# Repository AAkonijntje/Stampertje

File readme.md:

Project AAkonijntjes

## Abstract
In dit project maken we een robot genaamd Stampertje.
Axel Willekens en Arno Plaetinck aka AAkonijntjes

## Documentation

## Authors

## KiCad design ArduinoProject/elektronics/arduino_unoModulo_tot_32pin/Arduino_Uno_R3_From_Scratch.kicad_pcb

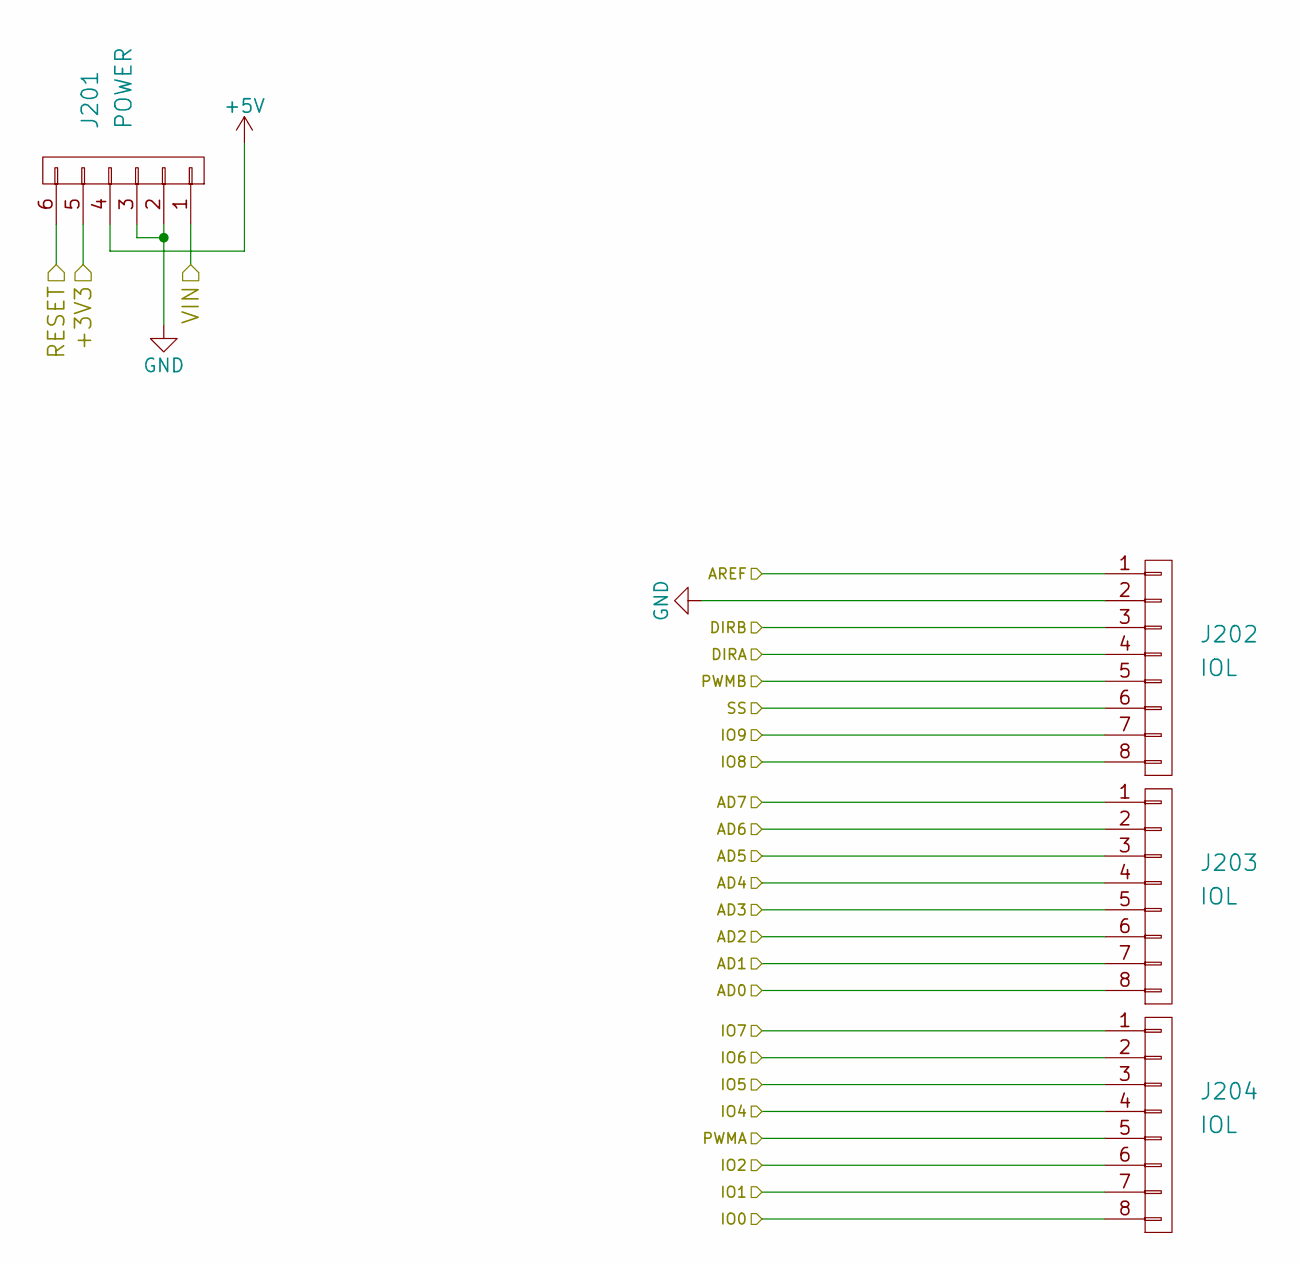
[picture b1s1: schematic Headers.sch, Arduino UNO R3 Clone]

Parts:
J201: POWER; Socket_Strip_Straight_1x06_Pitch2.54mm
J202, J203, J204: IOL; Socket_Strip_Straight_1x08_Pitch2.54mm

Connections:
328P_ICSP_MISO: J202.4; also elsewhere on the board
328P_ICSP_MOSI: J202.5; also elsewhere on the board
328P_ICSP_SCK: J202.3; also elsewhere on the board
+5V: J201.4; also elsewhere on the board
/ATMEGA328P/AD0: J203.8; also elsewhere on the board
/ATMEGA328P/AD1: J203.7; also elsewhere on the board
/ATMEGA328P/AD2: J203.6; also elsewhere on the board
/ATMEGA328P/AD3: J203.5; also elsewhere on the board
/ATMEGA328P/AD4: J203.4; also elsewhere on the board
/ATMEGA328P/AD5: J203.3; also elsewhere on the board
/ATMEGA328P/AD6: J203.2; also elsewhere on the board
/ATMEGA328P/AD7: J203.1; also elsewhere on the board
/ATMEGA328P/AREF: J202.1; also elsewhere on the board
/ATMEGA328P/IO0: J204.8; also elsewhere on the board
/ATMEGA328P/IO1: J204.7; also elsewhere on the board
/ATMEGA328P/IO2: J204.6; also elsewhere on the board
/ATMEGA328P/IO4: J204.4; also elsewhere on the board
/ATMEGA328P/IO5: J204.3; also elsewhere on the board
/ATMEGA328P/IO6: J204.2; also elsewhere on the board
/ATMEGA328P/IO7: J204.1; also elsewhere on the board
/ATMEGA328P/IO8: J202.8; also elsewhere on the board
/ATMEGA328P/IO9: J202.7; also elsewhere on the board
/ATMEGA328P/PWMA: J204.5; also elsewhere on the board
/ATMEGA328P/RESET: J201.6; also elsewhere on the board
/ATMEGA328P/SS: J202.6; also elsewhere on the board
/Headers/+3V3: J201.5; also elsewhere on the board
/Headers/VIN: J201.1; also elsewhere on the board
GND: J201.2, J201.3, J202.2; also elsewhere on the board

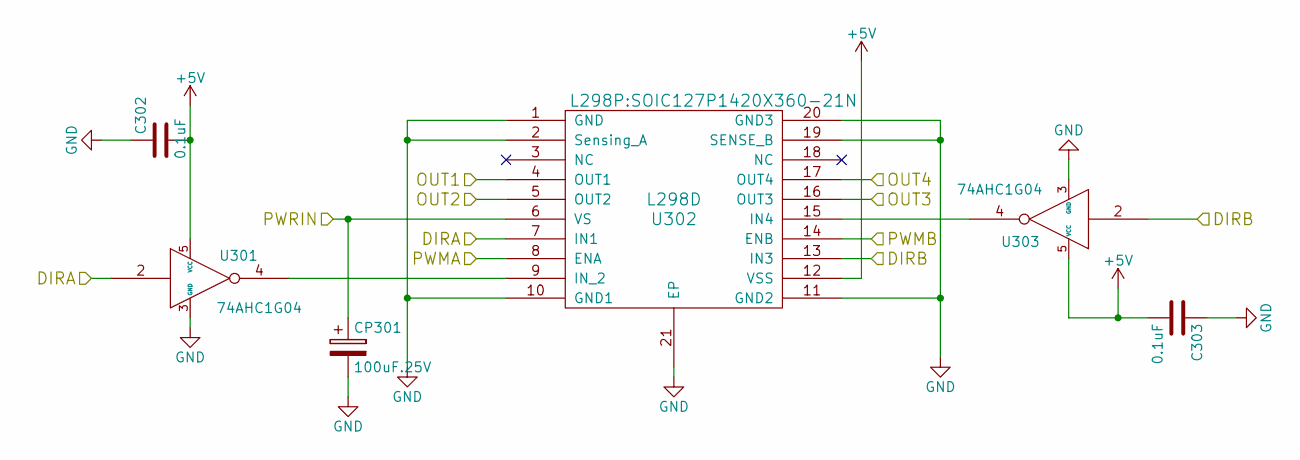
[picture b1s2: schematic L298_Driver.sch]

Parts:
C302, C303: 0.1uF; C_0805
CP301: 100uF.25V; CP_Elec_6.3x5.3
U301, U303: 74AHC1G04; SOT65P210X110-5N
U302: L298D; SOIC127P1420X360-21N

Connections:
328P_ICSP_MISO: U301.2, U302.7 (IN1); also elsewhere on the board
328P_ICSP_MOSI: U302.14 (ENB); also elsewhere on the board
328P_ICSP_SCK: U302.13 (IN3), U303.2; also elsewhere on the board
+5V: C302.2, C303.2, U301.5 (VCC), U302.12 (VSS), U303.5 (VCC); also elsewhere on the board
/ATMEGA328P/PWMA: U302.8 (ENA); also elsewhere on the board
/L298_Driver./OUT1: U302.4 (OUT1); also elsewhere on the board
/L298_Driver./OUT2: U302.5 (OUT2); also elsewhere on the board
/L298_Driver./OUT3: U302.16 (OUT3); also elsewhere on the board
/L298_Driver./OUT4: U302.17 (OUT4); also elsewhere on the board
/L298_Driver./PWRIN: CP301.1, U302.6 (VS); also elsewhere on the board
GND: C302.1, C303.1, CP301.2, U301.3 (GND), U302.1 (GND), U302.2 (Sensing_A), U302.10 (GND1), U302.11 (GND2), U302.19 (SENSE_B), U302.20 (GND3), U302.21 (EP), U303.3 (GND); also elsewhere on the board
unnamed: U301.4, U302.9 (IN_2)
unnamed: U302.15 (IN4), U303.4

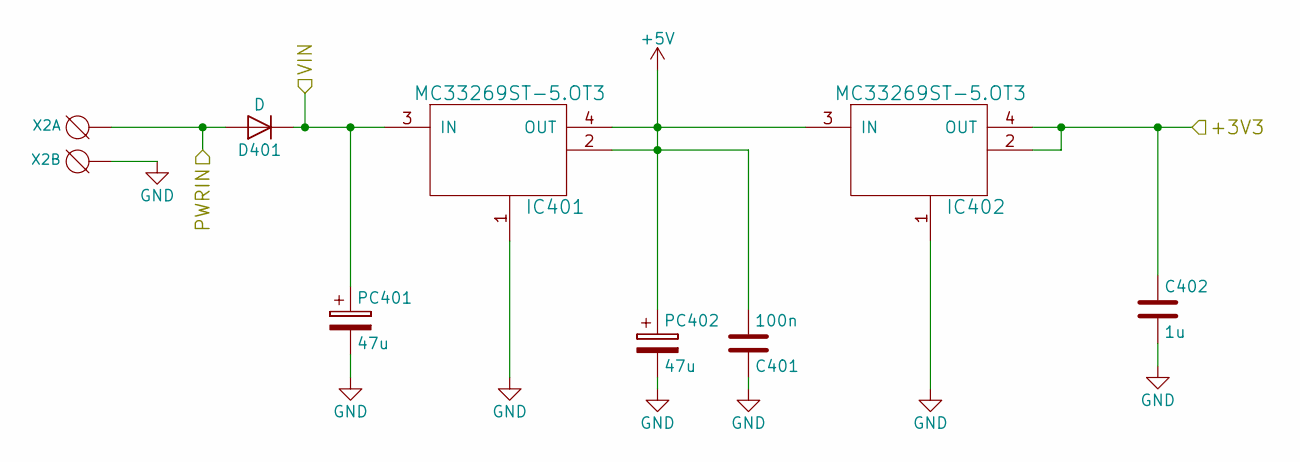
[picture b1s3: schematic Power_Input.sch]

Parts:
C401: 100n; C_0805
C402: 1u; C_0805
D401: D; D_MiniMELF_Handsoldering
IC401, IC402: MC33269ST-5.OT3; SOT230P700X180-4N
PC401, PC402: 47u; CP_Elec_6.3x5.3
X2: DG3XX-02-3.5; degson-DG350-3.5-02P

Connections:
+5V: C401.2, IC401.2, IC401.4 (OUT), IC402.3 (IN), PC402.1; also elsewhere on the board
/Headers/+3V3: C402.1, IC402.2, IC402.4 (OUT); also elsewhere on the board
/Headers/VIN: D401.1 (K), IC401.3 (IN), PC401.1; also elsewhere on the board
/L298_Driver./PWRIN: D401.2 (A), X2.1; also elsewhere on the board
GND: C401.1, C402.2, IC401.1, IC402.1, PC401.2, PC402.2, X2.2; also elsewhere on the board

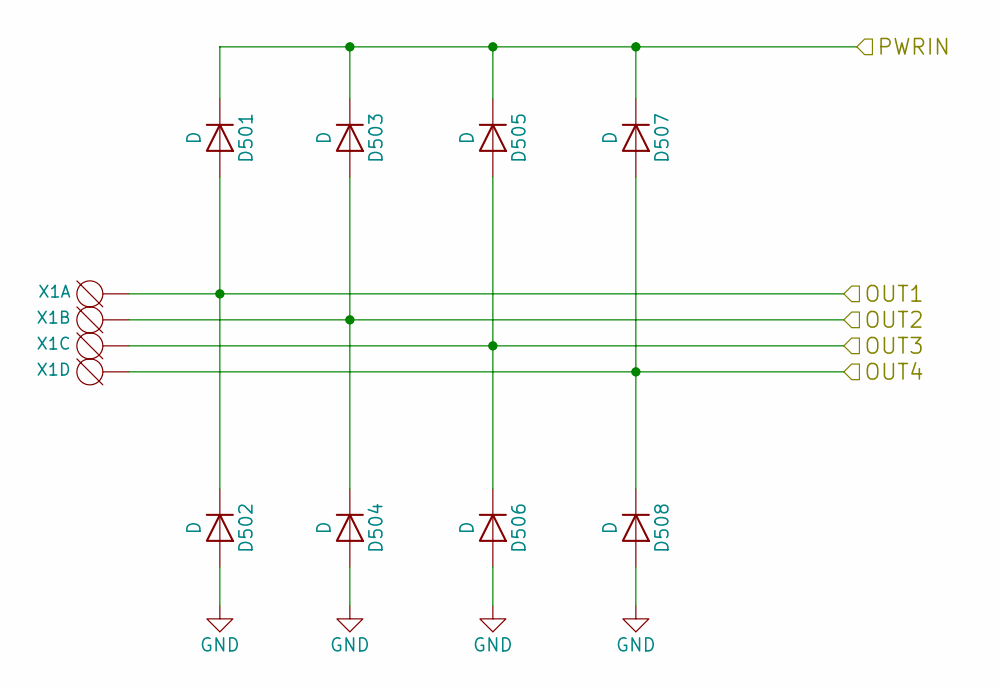
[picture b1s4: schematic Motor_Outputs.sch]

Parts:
D501, D502, D503, D504, D505, D506, D507, D508: D; DIOM5437X240N
X1: DG3XX-04-3.5; degson-DG350-3.5-04P

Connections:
/L298_Driver./OUT1: D501.2 (A), D502.1 (K), X1.1; also elsewhere on the board
/L298_Driver./OUT2: D503.2 (A), D504.1 (K), X1.2; also elsewhere on the board
/L298_Driver./OUT3: D505.2 (A), D506.1 (K), X1.3; also elsewhere on the board
/L298_Driver./OUT4: D507.2 (A), D508.1 (K), X1.4; also elsewhere on the board
/L298_Driver./PWRIN: D501.1 (K), D503.1 (K), D505.1 (K), D507.1 (K); also elsewhere on the board
GND: D502.2 (A), D504.2 (A), D506.2 (A), D508.2 (A); also elsewhere on the board

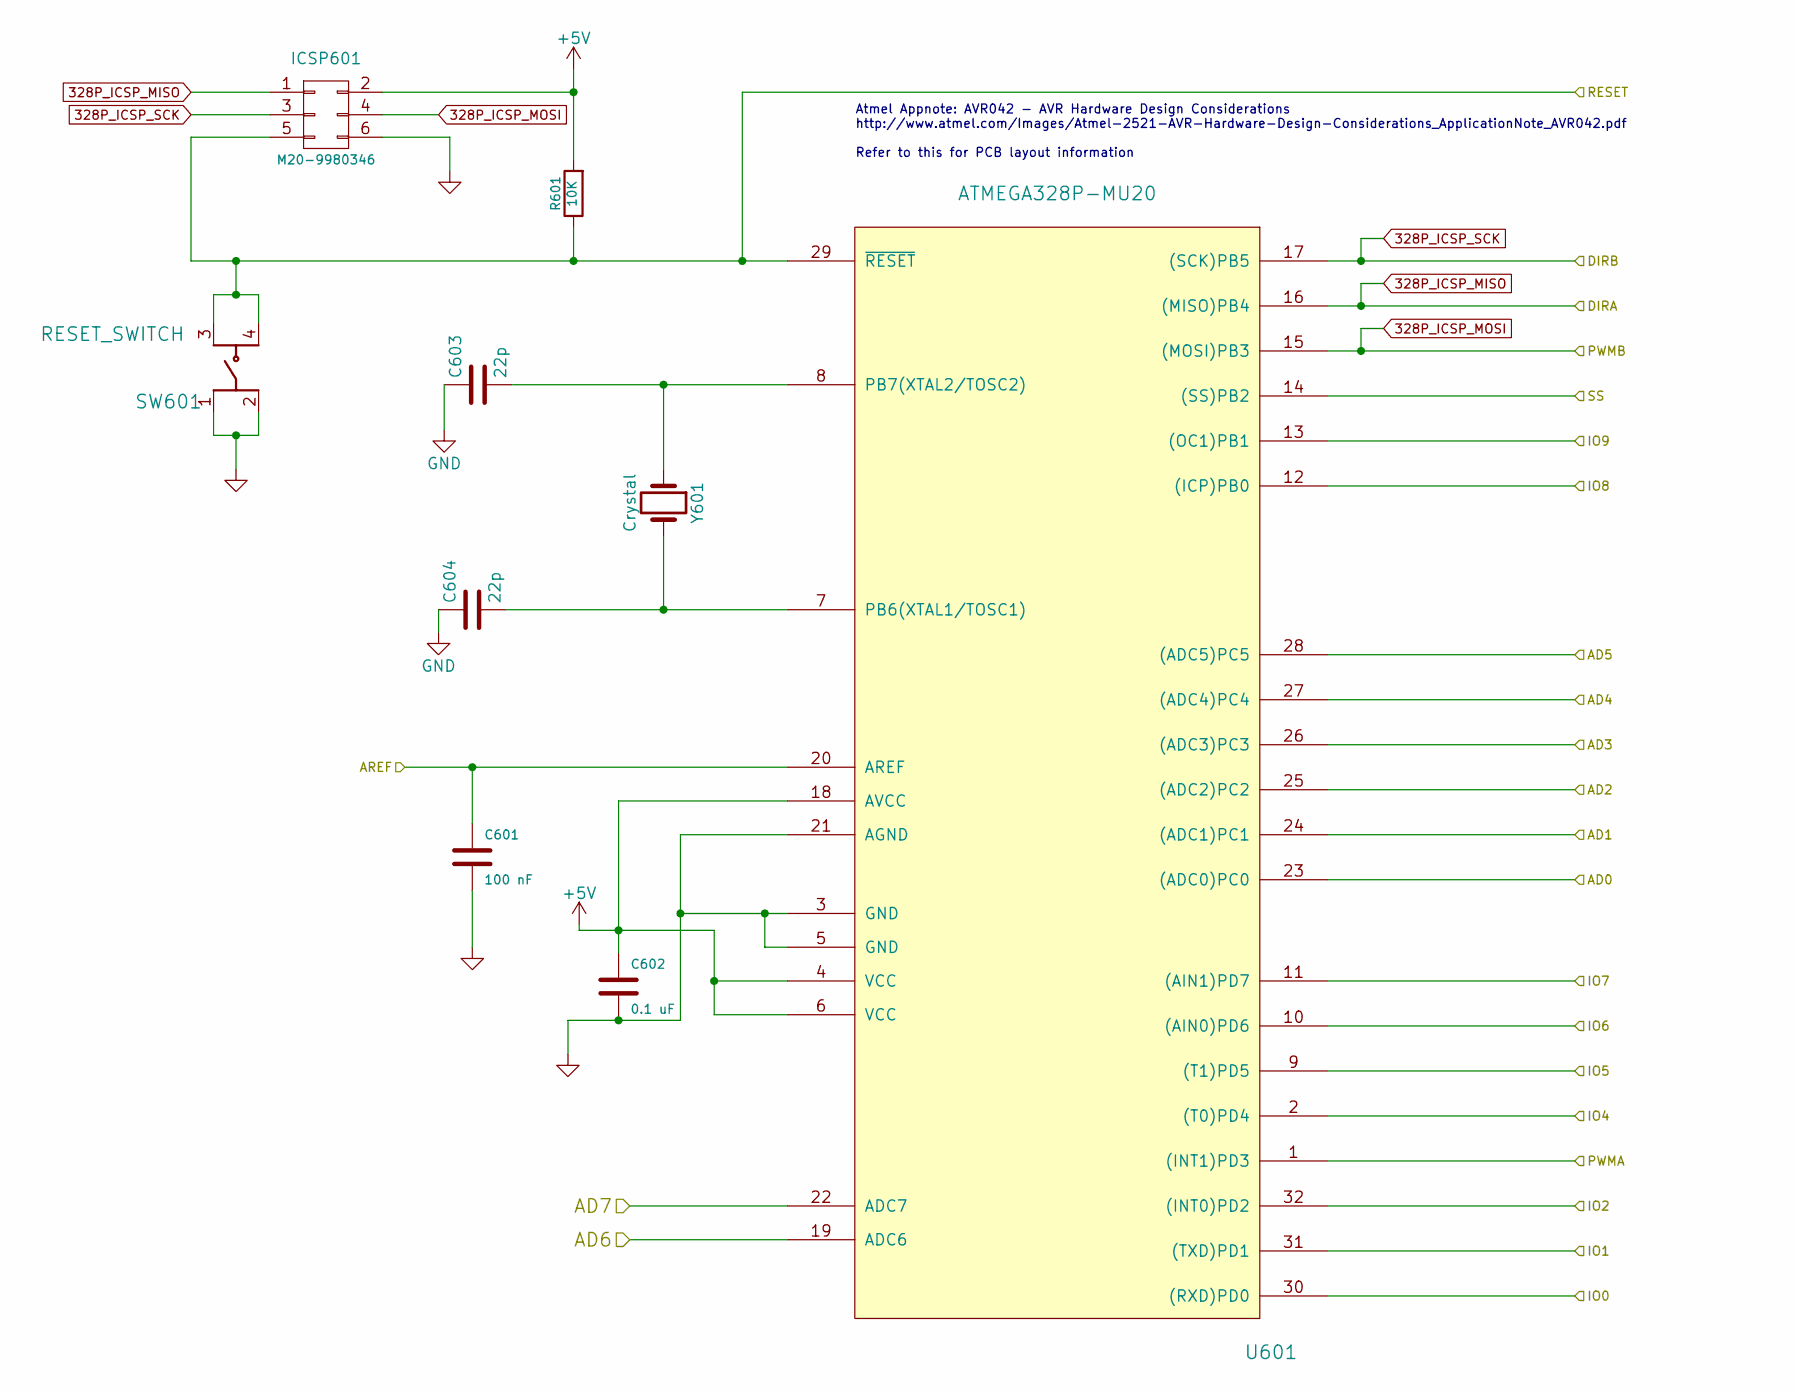
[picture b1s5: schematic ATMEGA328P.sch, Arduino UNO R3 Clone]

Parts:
C601: 100 nF; C_0805
C602: 0.1 uF; C_0805
C603, C604: 22p; C_0805
ICSP601: M20-9980346; HDRV6W64P254_2X3_762X508X868P
R601: 10K; R_0805
SW601: RESET_SWITCH; FSM-SWITCH
U601: ATMEGA328P-MU20; QFP80P900X900X120-32N
Y601: Crystal; HC%2f49US-(AT49)_1

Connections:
328P_ICSP_MISO: ICSP601.1, U601.16 ((MISO)PB4); also elsewhere on the board
328P_ICSP_MOSI: ICSP601.4, U601.15 ((MOSI)PB3); also elsewhere on the board
328P_ICSP_SCK: ICSP601.3, U601.17 ((SCK)PB5); also elsewhere on the board
+5V: C602.1, ICSP601.2, R601.2, U601.4 (VCC), U601.6 (VCC), U601.18 (AVCC); also elsewhere on the board
/ATMEGA328P/AD0: U601.23 ((ADC0)PC0); also elsewhere on the board
/ATMEGA328P/AD1: U601.24 ((ADC1)PC1); also elsewhere on the board
/ATMEGA328P/AD2: U601.25 ((ADC2)PC2); also elsewhere on the board
/ATMEGA328P/AD3: U601.26 ((ADC3)PC3); also elsewhere on the board
/ATMEGA328P/AD4: U601.27 ((ADC4)PC4); also elsewhere on the board
/ATMEGA328P/AD5: U601.28 ((ADC5)PC5); also elsewhere on the board
/ATMEGA328P/AD6: U601.19 (ADC6); also elsewhere on the board
/ATMEGA328P/AD7: U601.22 (ADC7); also elsewhere on the board
/ATMEGA328P/AREF: C601.1, U601.20 (AREF); also elsewhere on the board
/ATMEGA328P/IO0: U601.30 ((RXD)PD0); also elsewhere on the board
/ATMEGA328P/IO1: U601.31 ((TXD)PD1); also elsewhere on the board
/ATMEGA328P/IO2: U601.32 ((INT0)PD2); also elsewhere on the board
/ATMEGA328P/IO4: U601.2 ((T0)PD4); also elsewhere on the board
/ATMEGA328P/IO5: U601.9 ((T1)PD5); also elsewhere on the board
/ATMEGA328P/IO6: U601.10 ((AIN0)PD6); also elsewhere on the board
/ATMEGA328P/IO7: U601.11 ((AIN1)PD7); also elsewhere on the board
/ATMEGA328P/IO8: U601.12 ((ICP)PB0); also elsewhere on the board
/ATMEGA328P/IO9: U601.13 ((OC1)PB1); also elsewhere on the board
/ATMEGA328P/PWMA: U601.1 ((INT1)PD3); also elsewhere on the board
/ATMEGA328P/RESET: ICSP601.5, R601.1, SW601.3, SW601.4, U601.29 (~RESET); also elsewhere on the board
/ATMEGA328P/SS: U601.14 ((SS)PB2); also elsewhere on the board
GND: C601.2, C602.2, C603.1, C604.1, ICSP601.6, SW601.1, SW601.2, U601.3 (GND), U601.5 (GND), U601.21 (AGND); also elsewhere on the board
unnamed: C603.2, U601.8 (PB7(XTAL2/TOSC2)), Y601.1
unnamed: C604.2, U601.7 (PB6(XTAL1/TOSC1)), Y601.2

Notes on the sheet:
Atmel Appnote: AVR042 - AVR Hardware Design Considerations http://www.atmel.com/Images/Atmel-2521-AVR-Hardware-Design-Considerations_ApplicationNote_AVR042.pdf Refer to this for PCB layout information

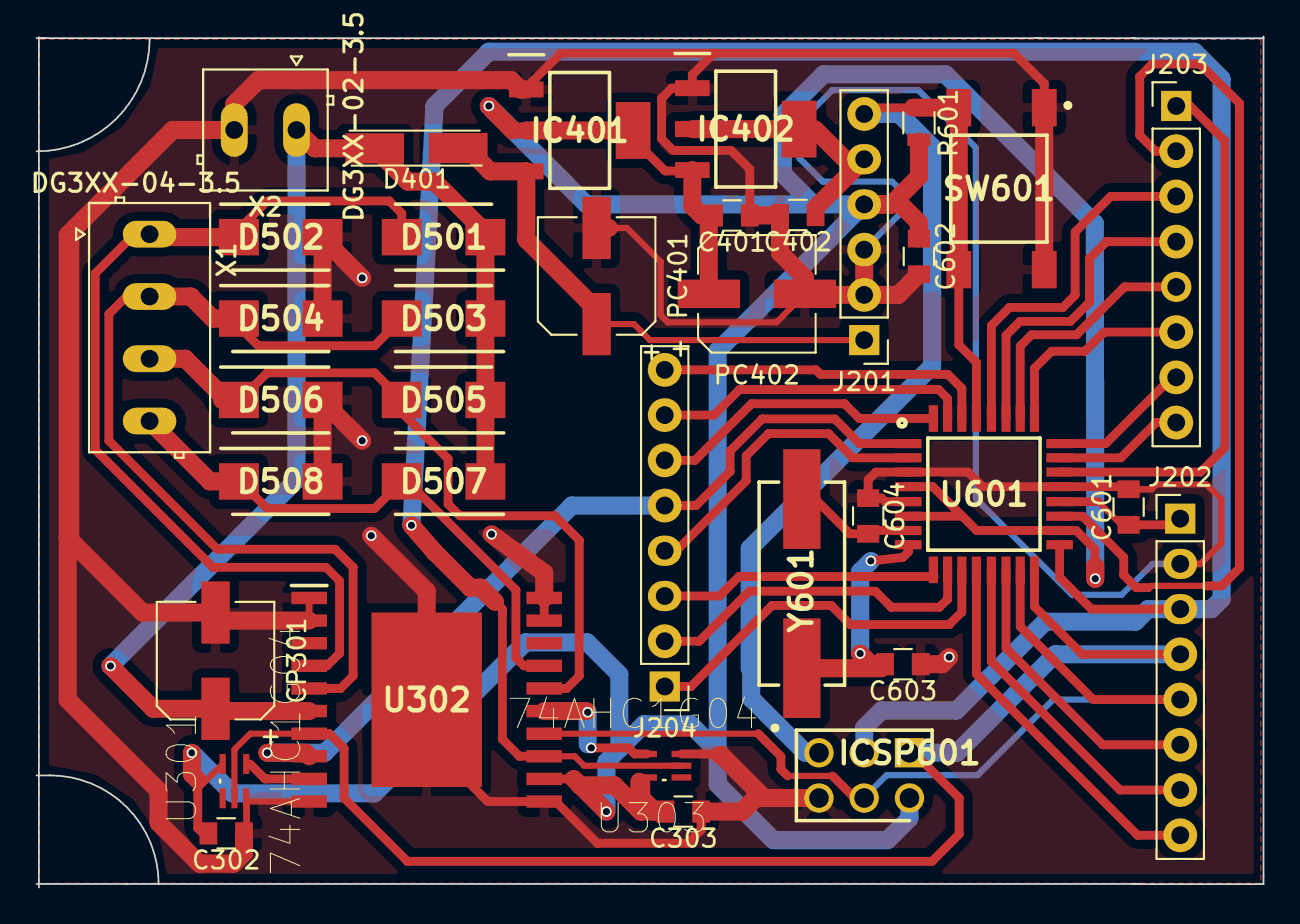
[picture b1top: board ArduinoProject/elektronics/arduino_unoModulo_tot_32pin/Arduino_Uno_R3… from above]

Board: 2 copper layers, 68.9 x 47.8 mm, 36 parts (0 on the bottom side), 37 nets.

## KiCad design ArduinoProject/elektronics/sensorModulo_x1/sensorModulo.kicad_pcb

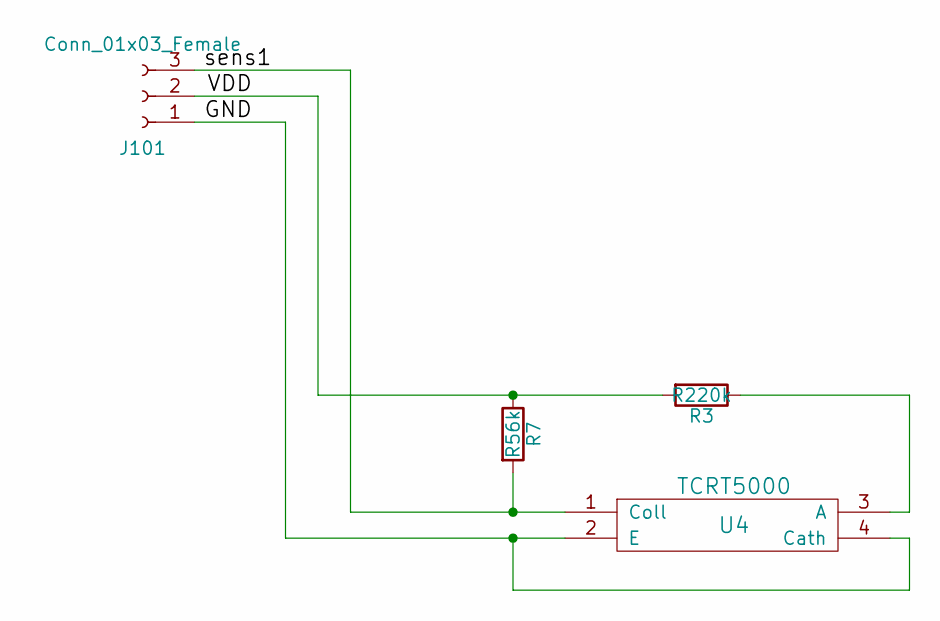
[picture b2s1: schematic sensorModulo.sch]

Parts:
J101: Conn_01x03_Female; Socket_Strip_Angled_1x03_Pitch2.54mm
R3: R220k; R_Axial_DIN0207_L6.3mm_D2.5mm_P10.16mm_Horizontal
R7: R56k; R_Axial_DIN0207_L6.3mm_D2.5mm_P10.16mm_Horizontal
U4: TCRT5000; TRTC5000

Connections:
/GND: J101.1, U4.2 (E), U4.4 (Cath)
/VDD: J101.2, R3.2, R7.1
/sens1: J101.3, R7.2, U4.1 (Coll)
unnamed: R3.1, U4.3 (A)

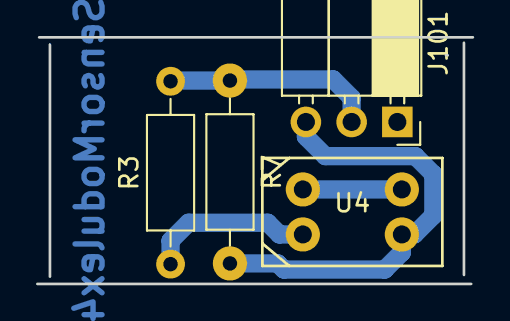
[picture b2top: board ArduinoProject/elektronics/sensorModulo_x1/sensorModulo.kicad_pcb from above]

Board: 2 copper layers, 24.2 x 13.7 mm, 4 parts (0 on the bottom side), 4 nets.

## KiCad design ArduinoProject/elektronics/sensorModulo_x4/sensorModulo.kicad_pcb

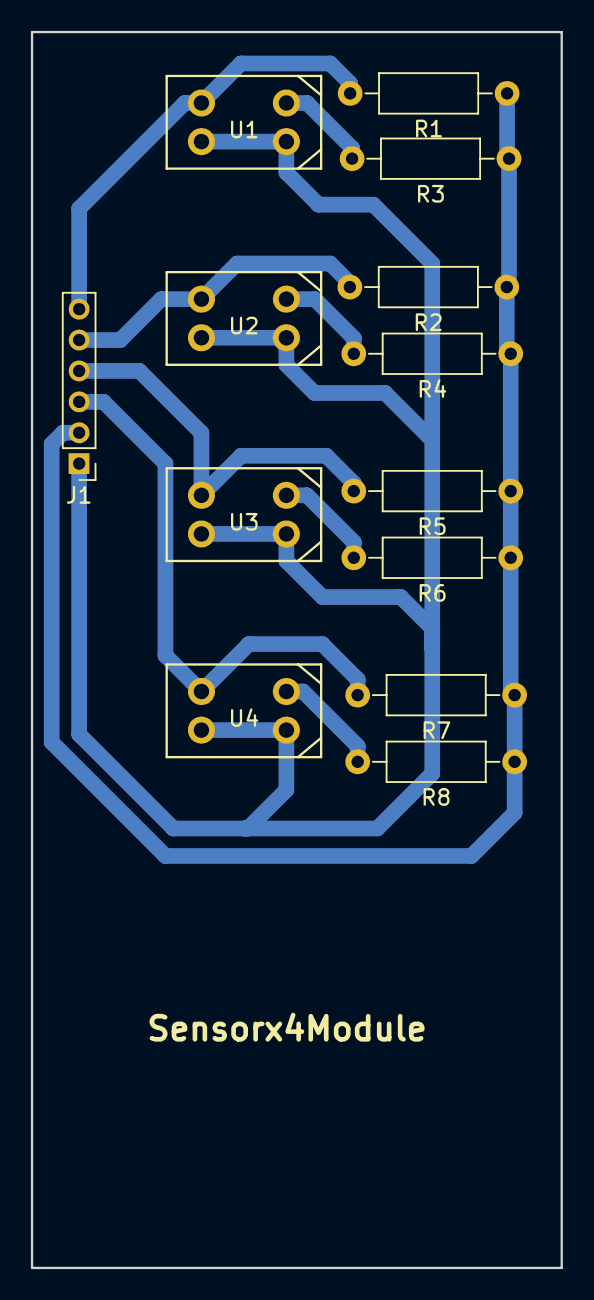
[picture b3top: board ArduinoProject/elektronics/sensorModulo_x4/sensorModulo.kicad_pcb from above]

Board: 2 copper layers, 34.3 x 80.0 mm, 13 parts (0 on the bottom side), 10 nets.

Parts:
J1: Conn_01x06_Female; Socket_Strip_Straight_1x06_Pitch2.00mm
R1, R2, R5, R7: R56k; R_Axial_DIN0207_L6.3mm_D2.5mm_P10.16mm_Horizontal
R3, R4, R6, R8: R220k; R_Axial_DIN0207_L6.3mm_D2.5mm_P10.16mm_Horizontal
U1, U2, U3, U4: TCRT5000; TRTC5000

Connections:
/GND: J1.1, U1.2, U1.4, U2.2, U2.4, U3.2, U3.4, U4.2, U4.4
/VDD: J1.2, R1.1, R2.1, R3.1, R4.1, R5.1, R6.1, R7.1, R8.1
/sens1: J1.6, R1.2, U1.1
/sens2: J1.5, R2.2, U2.1
/sens3: J1.4, R5.2, U3.1
/sens4: J1.3, R7.2, U4.1
unnamed: R3.2, U1.3
unnamed: R4.2, U2.3
unnamed: R6.2, U3.3
unnamed: R8.2, U4.3

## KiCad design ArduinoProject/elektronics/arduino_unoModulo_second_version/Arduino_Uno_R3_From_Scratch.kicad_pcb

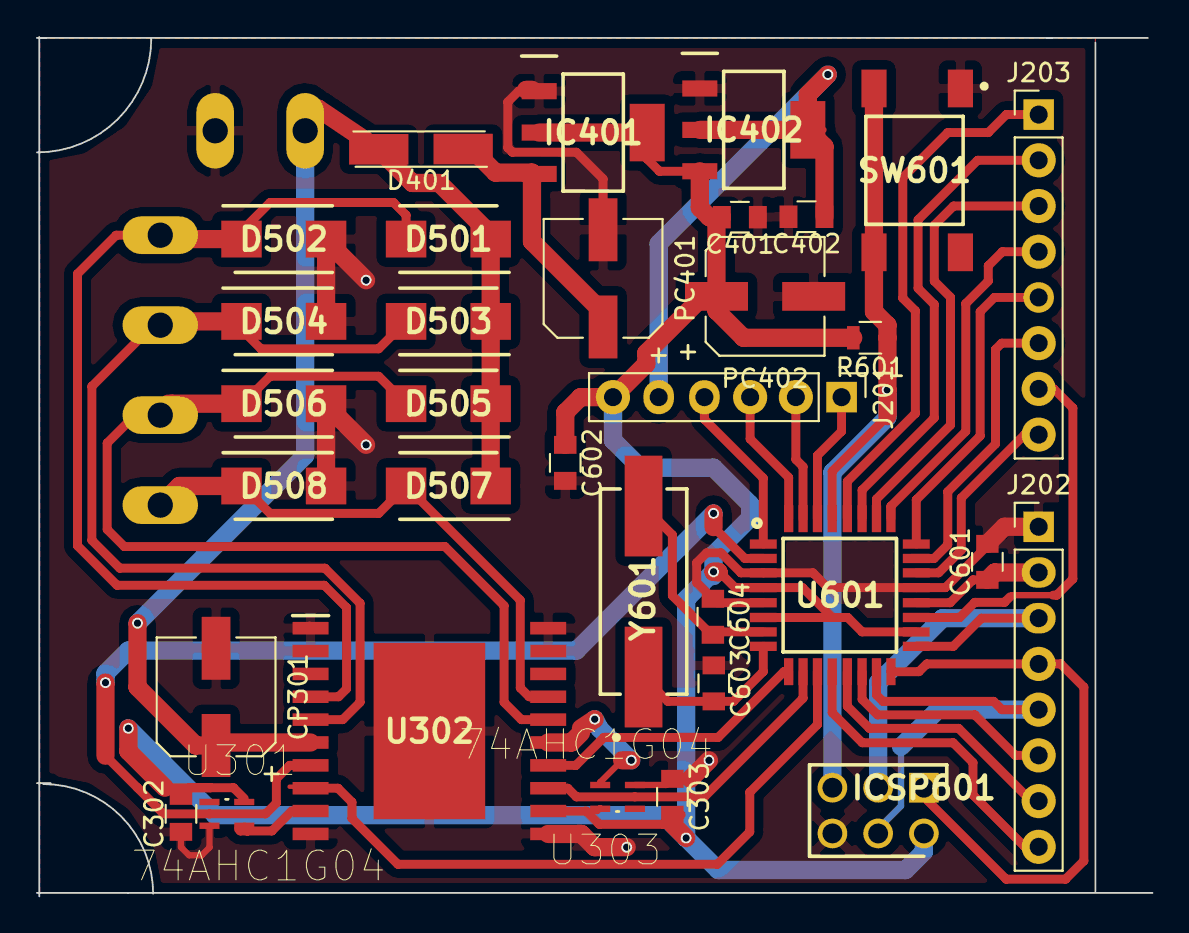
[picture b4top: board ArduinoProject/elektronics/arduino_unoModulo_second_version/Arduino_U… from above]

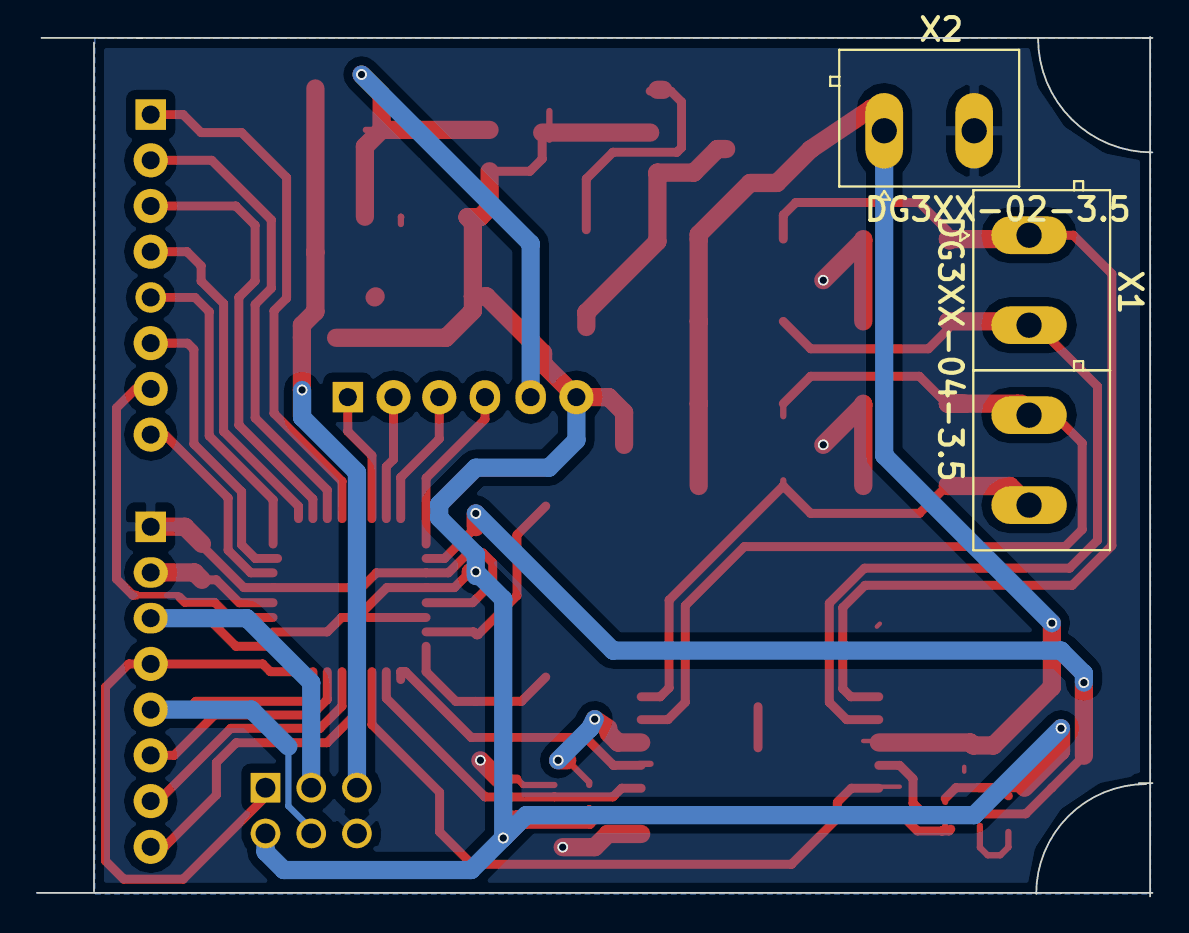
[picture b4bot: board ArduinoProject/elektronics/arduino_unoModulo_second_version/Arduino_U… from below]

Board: 2 copper layers, 62.0 x 47.8 mm, 35 parts (2 on the bottom side), 37 nets.

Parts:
C302, C303: 0.1uF; C_0805
C401: 100n; C_0805
C402: 1u; C_0805
C601: 100 nF; C_0805
C602: 0.1 uF; C_0805
C603, C604: 22p; C_0805
CP301: 100uF.25V; CP_Elec_6.3x5.3
D401: D; D_MiniMELF_Handsoldering
D501, D502, D503, D504, D505, D506, D507, D508: D; DIOM5437X240N
IC401, IC402: MC33269ST-5.OT3; SOT230P700X180-4N
ICSP601: M20-9980346; HDRV6W64P254_2X3_762X508X868P
J201: digitaal/voltages; Socket_Strip_Straight_1x06_Pitch2.54mm
J202: digital/gnd/aref; Socket_Strip_Straight_1x08_Pitch2.54mm
J203: analog; Socket_Strip_Straight_1x08_Pitch2.54mm
PC401, PC402: 47u; CP_Elec_6.3x5.3
R601: 10K; R_0805
SW601: RESET_SWITCH; FSM-SWITCH
U301, U303: 74AHC1G04; SOT65P210X110-5N
U302: L298D; SOIC127P1420X360-21N
U601: ATMEGA328P-MU20; QFP80P900X900X120-32N
X1: DG3XX-04-3.5; degson-DG306-5.0-04P
X2: DG3XX-02-3.5; degson-DG306-5.0-02P
Y601: Crystal; HC%2f49US-(AT49)_1

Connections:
328P_ICSP_MISO: ICSP601.1, J202.4, U601.16
328P_ICSP_MOSI: ICSP601.4, J202.5, U601.15
328P_ICSP_SCK: ICSP601.3, J202.3, U601.17
+5V: C302.2, C303.2, C401.2, C602.1, IC401.2, IC401.4, IC402.3, ICSP601.2, J201.6, PC402.1, R601.2, U301.5, U302.12, U303.5, U601.4, U601.6, U601.18
/ATMEGA328P/AD0: J203.6, U601.23
/ATMEGA328P/AD1: J203.5, U601.24
/ATMEGA328P/AD2: J203.4, U601.25
/ATMEGA328P/AD3: J203.3, U601.26
/ATMEGA328P/AD4: J203.2, U601.27
/ATMEGA328P/AD5: J203.1, U601.28
/ATMEGA328P/AD6: J203.7, U601.19
/ATMEGA328P/AD7: J203.8, U601.22
/ATMEGA328P/AREF: C601.1, J202.2, U601.20
/ATMEGA328P/DIRA: U301.2, U302.7, U601.2
/ATMEGA328P/DIRB: U302.13, U303.2, U601.10
/ATMEGA328P/IO0: J201.1, U601.30
/ATMEGA328P/IO1: J201.2, U601.31
/ATMEGA328P/IO2: J201.3, U601.32
/ATMEGA328P/IO3: J201.4, U601.1
/ATMEGA328P/IO8: J202.8, U601.12
/ATMEGA328P/IO9: J202.7, U601.13
/ATMEGA328P/PWMA: U302.8, U601.11
/ATMEGA328P/PWMB: U302.14, U601.9
/ATMEGA328P/SS: J202.6, U601.14
/Headers/+3V3: C402.1, IC402.2, IC402.4, J201.5
/L298_Driver./OUT1: D501.2, D502.1, U302.4, X1.1
/L298_Driver./OUT2: D503.2, D504.1, U302.5, X1.2
/L298_Driver./OUT3: D505.2, D506.1, U302.16, X1.3
/L298_Driver./OUT4: D507.2, D508.1, U302.17, X1.4
/L298_Driver./PWRIN: CP301.1, D401.2, D501.1, D503.1, D505.1, D507.1, U302.6, X2.1
GND: C302.1, C303.1, C401.1, C402.2, C601.2, C602.2, C603.1, C604.1, CP301.2, D502.2, D504.2, D506.2, D508.2, IC401.1, IC402.1, ICSP601.6, J202.1, PC401.2, PC402.2, SW601.1, U301.3, U302.1, U302.2, U302.10, U302.11, U302.19, U302.20, U302.21, U303.3, U601.3, U601.5, U601.21, X2.2
unnamed: C603.2, U601.8, Y601.1
unnamed: C604.2, U601.7, Y601.2
unnamed: D401.1, IC401.3, PC401.1
unnamed: ICSP601.5, R601.1, SW601.3, SW601.4, U601.29
unnamed: U301.4, U302.9
unnamed: U302.15, U303.4

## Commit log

2017-11-07 readme.md added
2017-11-07 added planning
2017-11-07 extra info
2017-11-07 altered charter
2017-11-07 Ex2: Arduino
    nieuwe map volgens ex 2
2017-11-07 naamverandering lib
2017-11-07 blink.h added
2017-11-07 basisbestandstructuur geïmplementeerd
2017-11-08 arduino electronics added
2017-11-08 schema arduino altered
2017-11-08 Toevoegen Lib L298
2017-11-08 verwijderen foute lib
2017-11-08 added EEGsschema l298
2017-11-08 l298 juiste lib toevoegen
2017-11-08 documentation added
2017-11-08 Schema driver l298
2017-11-08 DriverProtectionAndOutput EEGschema
2017-11-08 Token
2017-11-09 link.txt toegevoegd
2017-11-09 doc ArduinoProject/elektronics altered
2017-11-09 jklm
2017-11-09 lib map verwijderd lib verplaatst naar main
2017-11-09 library opmaken
2017-11-09 sensorModulo added
2018-02-14 Toevoeging brolmapje
2018-02-14 arduino aanpassingen
2018-02-18 arduino_uno gewijzigd
2018-02-21 Update arduino main code
2018-02-21 timer3 library added
2018-02-21 update arduino
2018-02-21 altered kicad
2018-02-23 WERKENDE ROBOT CODE
2018-02-26 arduino code met PID
2018-02-26 arduino code met PID2
2018-02-26 arduino code met PID3
2018-02-27 arduino code met PID4
2018-02-28 kicad schema altered: alles op 1 PCB
2018-02-28 kicad schema altered: alles op 1 PCB2
2018-02-28 kicad schema altered: alles op 1 PCB3
2018-02-28 PID code altered
2018-02-28 programmeren
2018-03-02 digitale_vesie_met_PID added
2018-03-02 digitale_vesie_met_PID added2
2018-03-06 arduino 32pin added
2018-03-06 analog pins added
2018-03-07 digitale_versie_met_PID2 added
2018-03-07 digitale_versie_met_PID2 added altered
2018-03-07 sensormodule_x4 added
2018-03-08 pid_4_sens added
2018-03-10 arduino routed
2018-03-10 arduino routint altered
2018-03-10 arduino routint altered2
2018-03-12 arduino footprint altered
2018-03-12 arduino footprint altered2
2018-03-12 arduino footprint altered3
2018-03-13 arduino footprint altered4
2018-03-13 arduino footprint altered5
2018-03-14 new components
2018-03-14 new components2
2018-03-14 correct components3
2018-03-14 modulo vier
2018-03-15 modulo4x
2018-03-15 sensorx4module
2018-03-15 codesensx4 altered
2018-03-15 update arduinocode
2018-03-15 sensorx4module_new
2018-03-16 arduino altered
2018-03-16 arduinocodeupdate
2018-03-16 baanbreedte verdikt
2018-03-16 padwith altered
2018-03-16 diode changed
2018-03-16 vias dik
2018-03-21 sensormodule rechts added
2018-03-21 changes made
2018-03-23 chaged printplaat'
2018-03-23 last changes
2018-03-28 werkende arduino code twee modules
2018-03-28 snelheidssensor
2018-03-30 last change working arduino
2018-03-30 last change working arduino2
2018-03-30 RFID toevoegen
2018-04-04 second printplaat version added
2018-04-04 second printplaat version added2
2018-04-17 update arduino oude MFRC522code weg
2018-04-18 rfid
2018-04-18 lib toevoegen
2018-04-21 verslag
2018-04-21 snelheidsmeter added
2018-04-23 nog wat prutstkes
2018-04-26 opkuis
2018-05-07 bluetooth
